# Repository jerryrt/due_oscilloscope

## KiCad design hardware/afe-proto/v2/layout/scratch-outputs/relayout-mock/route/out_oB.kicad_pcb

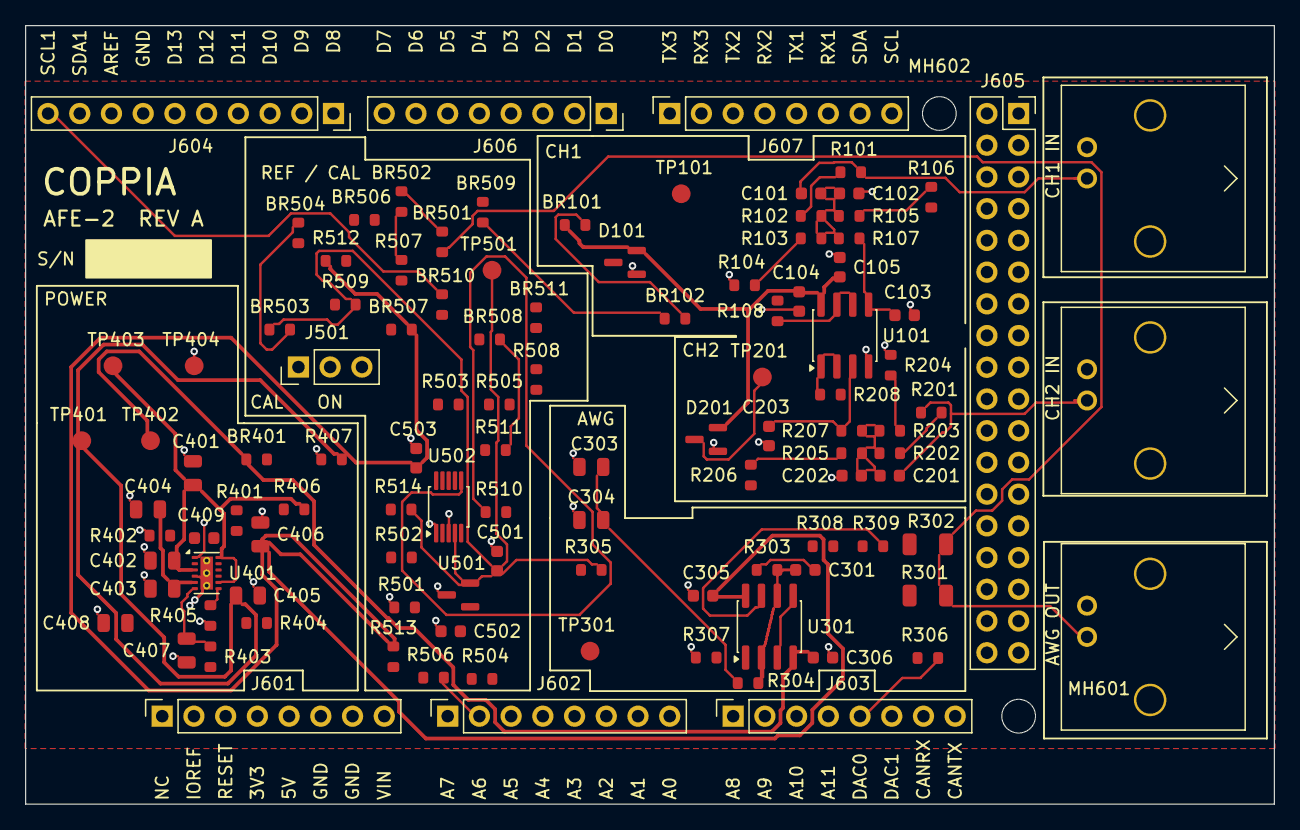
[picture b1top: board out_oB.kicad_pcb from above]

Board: 2 copper layers, 100.0 x 62.3 mm, 112 parts (0 on the bottom side), 61 nets.

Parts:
BR101, BR102, BR401, BR501, BR502, BR503, BR504, BR506, BR507, BR508, BR509, BR510, BR511: 0R; R_0603_1608Metric
C101, C201: 18p C0G; C_0603_1608Metric
C102, C202: 47p C0G; C_0603_1608Metric
C103, C203, C301: 10p C0G; C_0603_1608Metric
C104, C305, C306, C502, C503: 100n X7R; C_0603_1608Metric
C105, C409, C501: 1u X5R; C_0603_1608Metric
C303, C304, C401, C402, C403, C404, C405, C406, C407, C408: 10u X5R 25V; C_0805_2012Metric
D101, D201: BAV99; SOT-23
J101, J201, J301: KH-BNC50-3511; BNC_Kinghelm_KH-BNC50-3511_Horizontal
J501: CAL; PinHeader_1x03_P2.54mm_Vertical
J601: POWER0; PinSocket_1x08_P2.54mm_Vertical
J602: ADCL0; PinSocket_1x08_P2.54mm_Vertical
J603: ADCH0; PinSocket_1x08_P2.54mm_Vertical
J604: PWMH0; PinSocket_1x10_P2.54mm_Vertical
J605: XIO0; PinSocket_2x18_P2.54mm_Vertical_DueXIO
J606: PWML0; PinSocket_1x08_P2.54mm_Vertical
J607: COMMUNICATION0; PinSocket_1x08_P2.54mm_Vertical
MH601, MH602: M2.5 standoff; MountingHole_2.7mm_M2.5
R101, R103, R201, R203: 470k 1%; R_0603_1608Metric
R102, R202: 300k 1%; R_0603_1608Metric
R104, R105, R204, R205: 330k 1%; R_0603_1608Metric
R106, R206, R514: 0R; R_0603_1608Metric
R107, R207: 470R 1%; R_0603_1608Metric
R108, R208: 22R 1%; R_0603_1608Metric
R301, R302: 100R 1%; R_1206_3216Metric
R303, R304, R306: 3k 1%; R_0603_1608Metric
R305: 150R 1%; R_0603_1608Metric
R307: 27k 1%; R_0603_1608Metric
R308, R309, R406: 1R 1%; R_0603_1608Metric
R401: 120k 1%; R_0603_1608Metric
R402: 68k 1%; R_0603_1608Metric
R403: 56k 1%; R_0603_1608Metric
R404: 8.2k 1%; R_0603_1608Metric
R405: 100k 1%; R_0603_1608Metric
R407: 1.8k 1%; R_0603_1608Metric
R501, R502, R503, R504, R505, R506: 330R 1%; R_0603_1608Metric
R507: 15k 1%; R_0603_1608Metric
R508, R511: 10k 1%; R_0603_1608Metric
R509: 1k 1%; R_0603_1608Metric
R510: 3.9k 1%; R_0603_1608Metric
R512, R513: 4.7k 1%; R_0603_1608Metric
TP101: A1; TestPoint_Pad_D1.5mm
TP201: A0; TestPoint_Pad_D1.5mm
TP301: AWG_OUT; TestPoint_Pad_D1.5mm
TP401: +3V3A; TestPoint_Pad_D1.5mm
TP402: VNEG; TestPoint_Pad_D1.5mm
TP403: +5V_F; TestPoint_Pad_D1.5mm
TP404: GND; TestPoint_Pad_D1.5mm
TP501: VREF; TestPoint_Pad_D1.5mm
U101, U301: TPH2502-SR; SOIC-8_3.9x4.9mm_P1.27mm
U401: LM27762DSSR; WSON-12-1EP_3x2mm_P0.5mm_EP1x2.65_ThermalVias
U501: REF3030EAIDBZR; SOT-23
U502: ADS1115IDGSR; MSOP-10_3x3mm_P0.5mm

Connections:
/+3V3A: BR507.2, BR509.1, C305.1, C405.1, C406.1, C503.1, R401.1, R407.1, R512.1, R513.1, TP401.1, U301.8, U401.11, U502.8
/+3V3A_K: BR102.1, BR509.2
/+3V3A_R: BR507.1, C502.1, U501.1
/+3V3A_S: BR101.1, BR102.2
/+3V3A_U: BR101.2, C104.1, C105.1, D101.2, D201.2, U101.8
/+5V_DUE: J601.5, R406.1
/+5V_F: C401.1, C402.1, R406.2, TP403.1, U401.3, U401.8, U401.12
/A0: D201.3, J602.8, R208.2, TP201.1
/A1: D101.3, J602.7, R108.2, TP101.1
/ADS_B: R511.2, U502.7
/ADS_TAP: R510.2, U502.6
/AREF: J604.8, R514.2
/AWG_BIN: R306.2, R307.1, U301.3, U301.5
/AWG_BNC: BR501.2, J301.1, R301.2, R302.2
/AWG_BNC_L: BR502.1, R507.1
/AWG_BNC_M: BR501.1, BR502.2
/AWG_FB: C301.2, R303.2, R304.1, U301.2, U301.6
/AWG_OA: R308.1, U301.1
/AWG_OB: R309.1, U301.7
/AWG_VO: C301.1, R301.1, R302.1, R303.1, R308.2, R309.2, TP301.1
/AWG_VREF: C303.1, C304.1, R304.2, R305.2
/CH1_IN: C101.1, J101.1, R101.1
/CH1_M1: R101.2, R102.1
/CH1_M2: R103.2, R104.1
/CH1_M3: R105.2, R106.1
/CH1_N: C101.2, C102.1, R102.2, R103.1, R105.1, R107.1
/CH1_NP: C103.1, R107.2, U101.5
/CH1_OUT: R108.1, U101.6, U101.7
/CH2_IN: C201.1, J201.1, R201.1
/CH2_M1: R201.2, R202.1
/CH2_M2: R203.2, R204.1
/CH2_M3: R205.2, R206.1
/CH2_N: C201.2, C202.1, R202.2, R203.1, R205.1, R207.1
/CH2_NP: C203.1, R207.2, U101.3
/CH2_OUT: R208.1, U101.1, U101.2
/DAC0: J603.5, R306.1
/GND: C102.2, C103.2, C104.2, C105.2, C202.2, C203.2, C303.2, C304.2, C305.2, C306.2, C401.2, C402.2, C403.2, C404.2, C405.2, C406.2, C407.2, C408.2, C501.2, C502.2, C503.2, D101.1, D201.1, J101.2, J201.2, J301.2, J601.6, J601.7, J604.7, J605.35, J605.36, R104.2, R204.2, R307.2, R402.2, R405.2, R407.2, R501.1, TP404.1, U101.4, U401.1, U401.4, U401.13, U501.3, U502.1, U502.3
/LM_C1N: C409.2, U401.9
/LM_C1P: C409.1, U401.10
/LM_CP: C403.1, C404.1, U401.5
/LM_FB3M: R403.2, R404.1
/LM_FBN: R404.2, R405.1, U401.7
/LM_FBP: R401.2, R402.1, U401.2
/SCL: BR510.1, J604.10, R513.2
/SCL_A: BR510.2, U502.10
/SDA: BR511.1, J604.9
/SDA_A: BR511.2, R512.2, U502.9
/SNS_B: BR508.1, J501.2
/SNS_B_N: BR508.2, R508.2, R509.1, R511.1
/SNS_T0: R507.2, R508.1, R510.1
/TAP1: J602.6, R501.2, R502.1
/TAP2: J602.5, R502.2, R503.1
/TAP3: J501.3, J602.4, R503.2, R504.1
/TAP4: BR506.1, J501.1, J602.3, R504.2, R505.1
/TAP4_A: BR506.2, U502.5
/TAP5: J602.2, R505.2, R506.1
/VNEG: BR401.2, C306.1, TP402.1, U301.4
/VNEG_G: BR401.1, C407.1, C408.1, R403.1, U401.6
/VREF: BR503.1, C501.1, J602.1, R106.2, R305.1, R506.2, R509.2, R514.1, TP501.1, U501.2, U502.4
/VREF_M: BR503.2, BR504.1
/VREF_P: BR504.2, R206.2

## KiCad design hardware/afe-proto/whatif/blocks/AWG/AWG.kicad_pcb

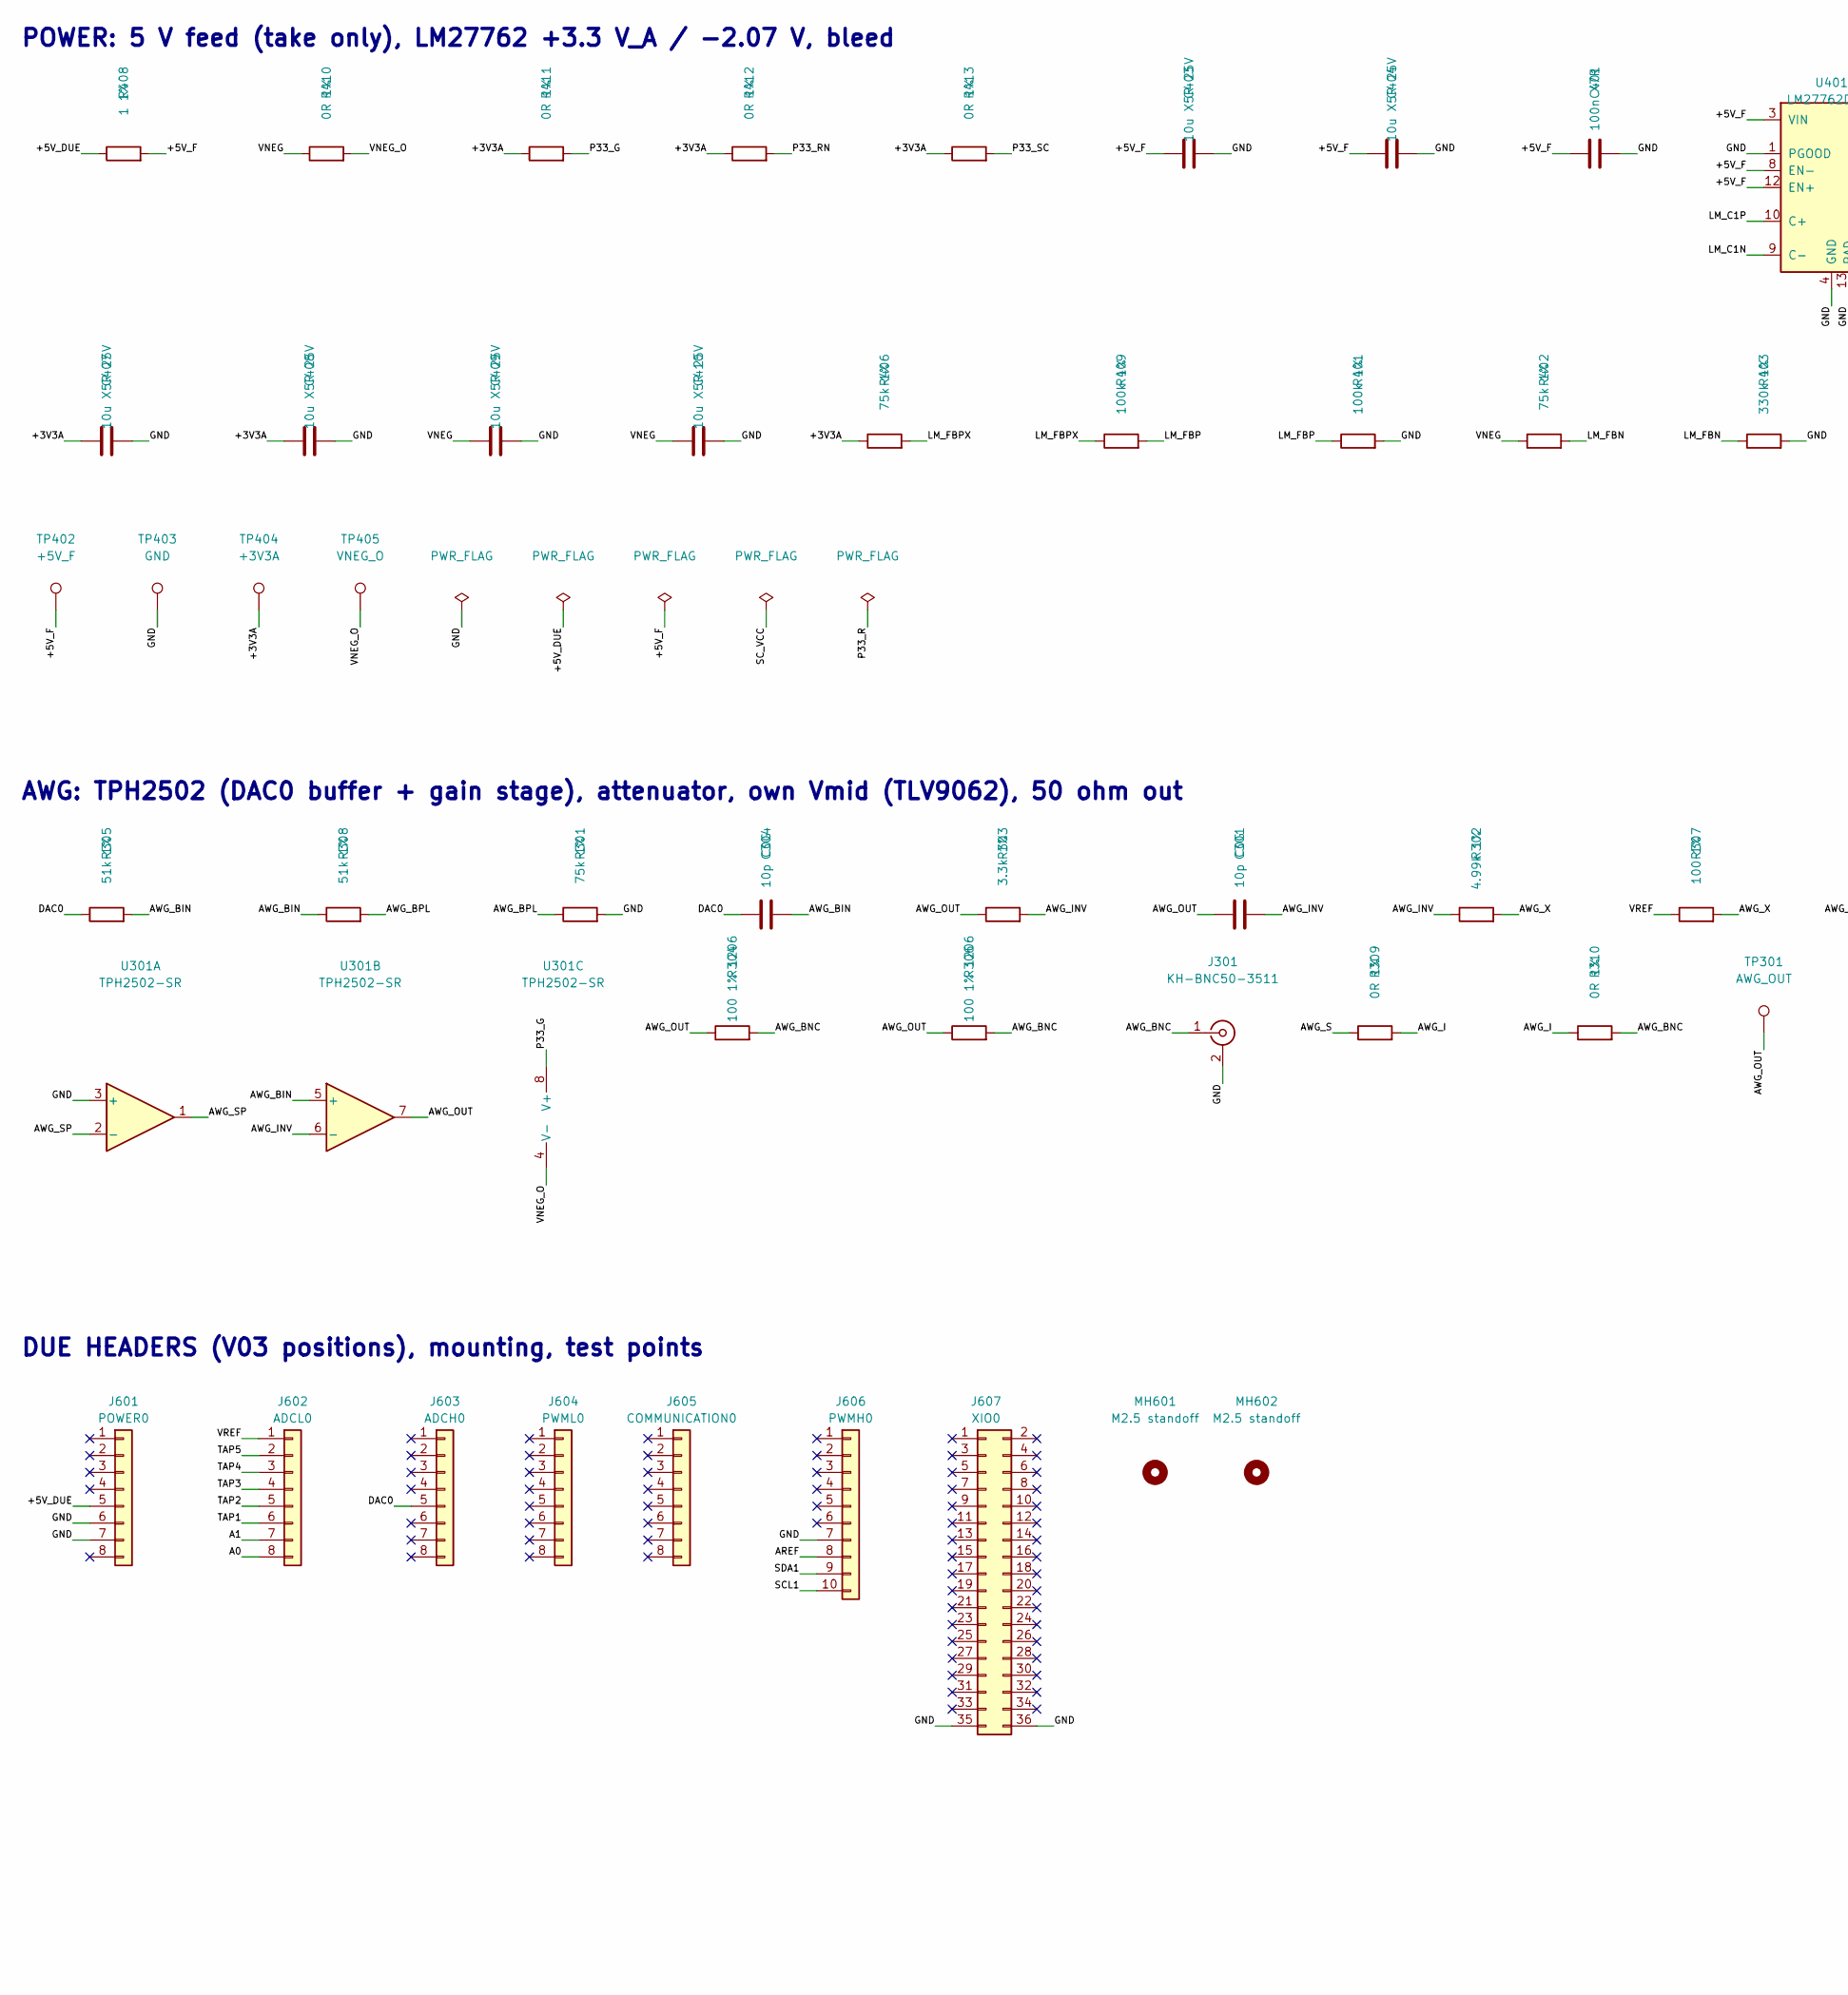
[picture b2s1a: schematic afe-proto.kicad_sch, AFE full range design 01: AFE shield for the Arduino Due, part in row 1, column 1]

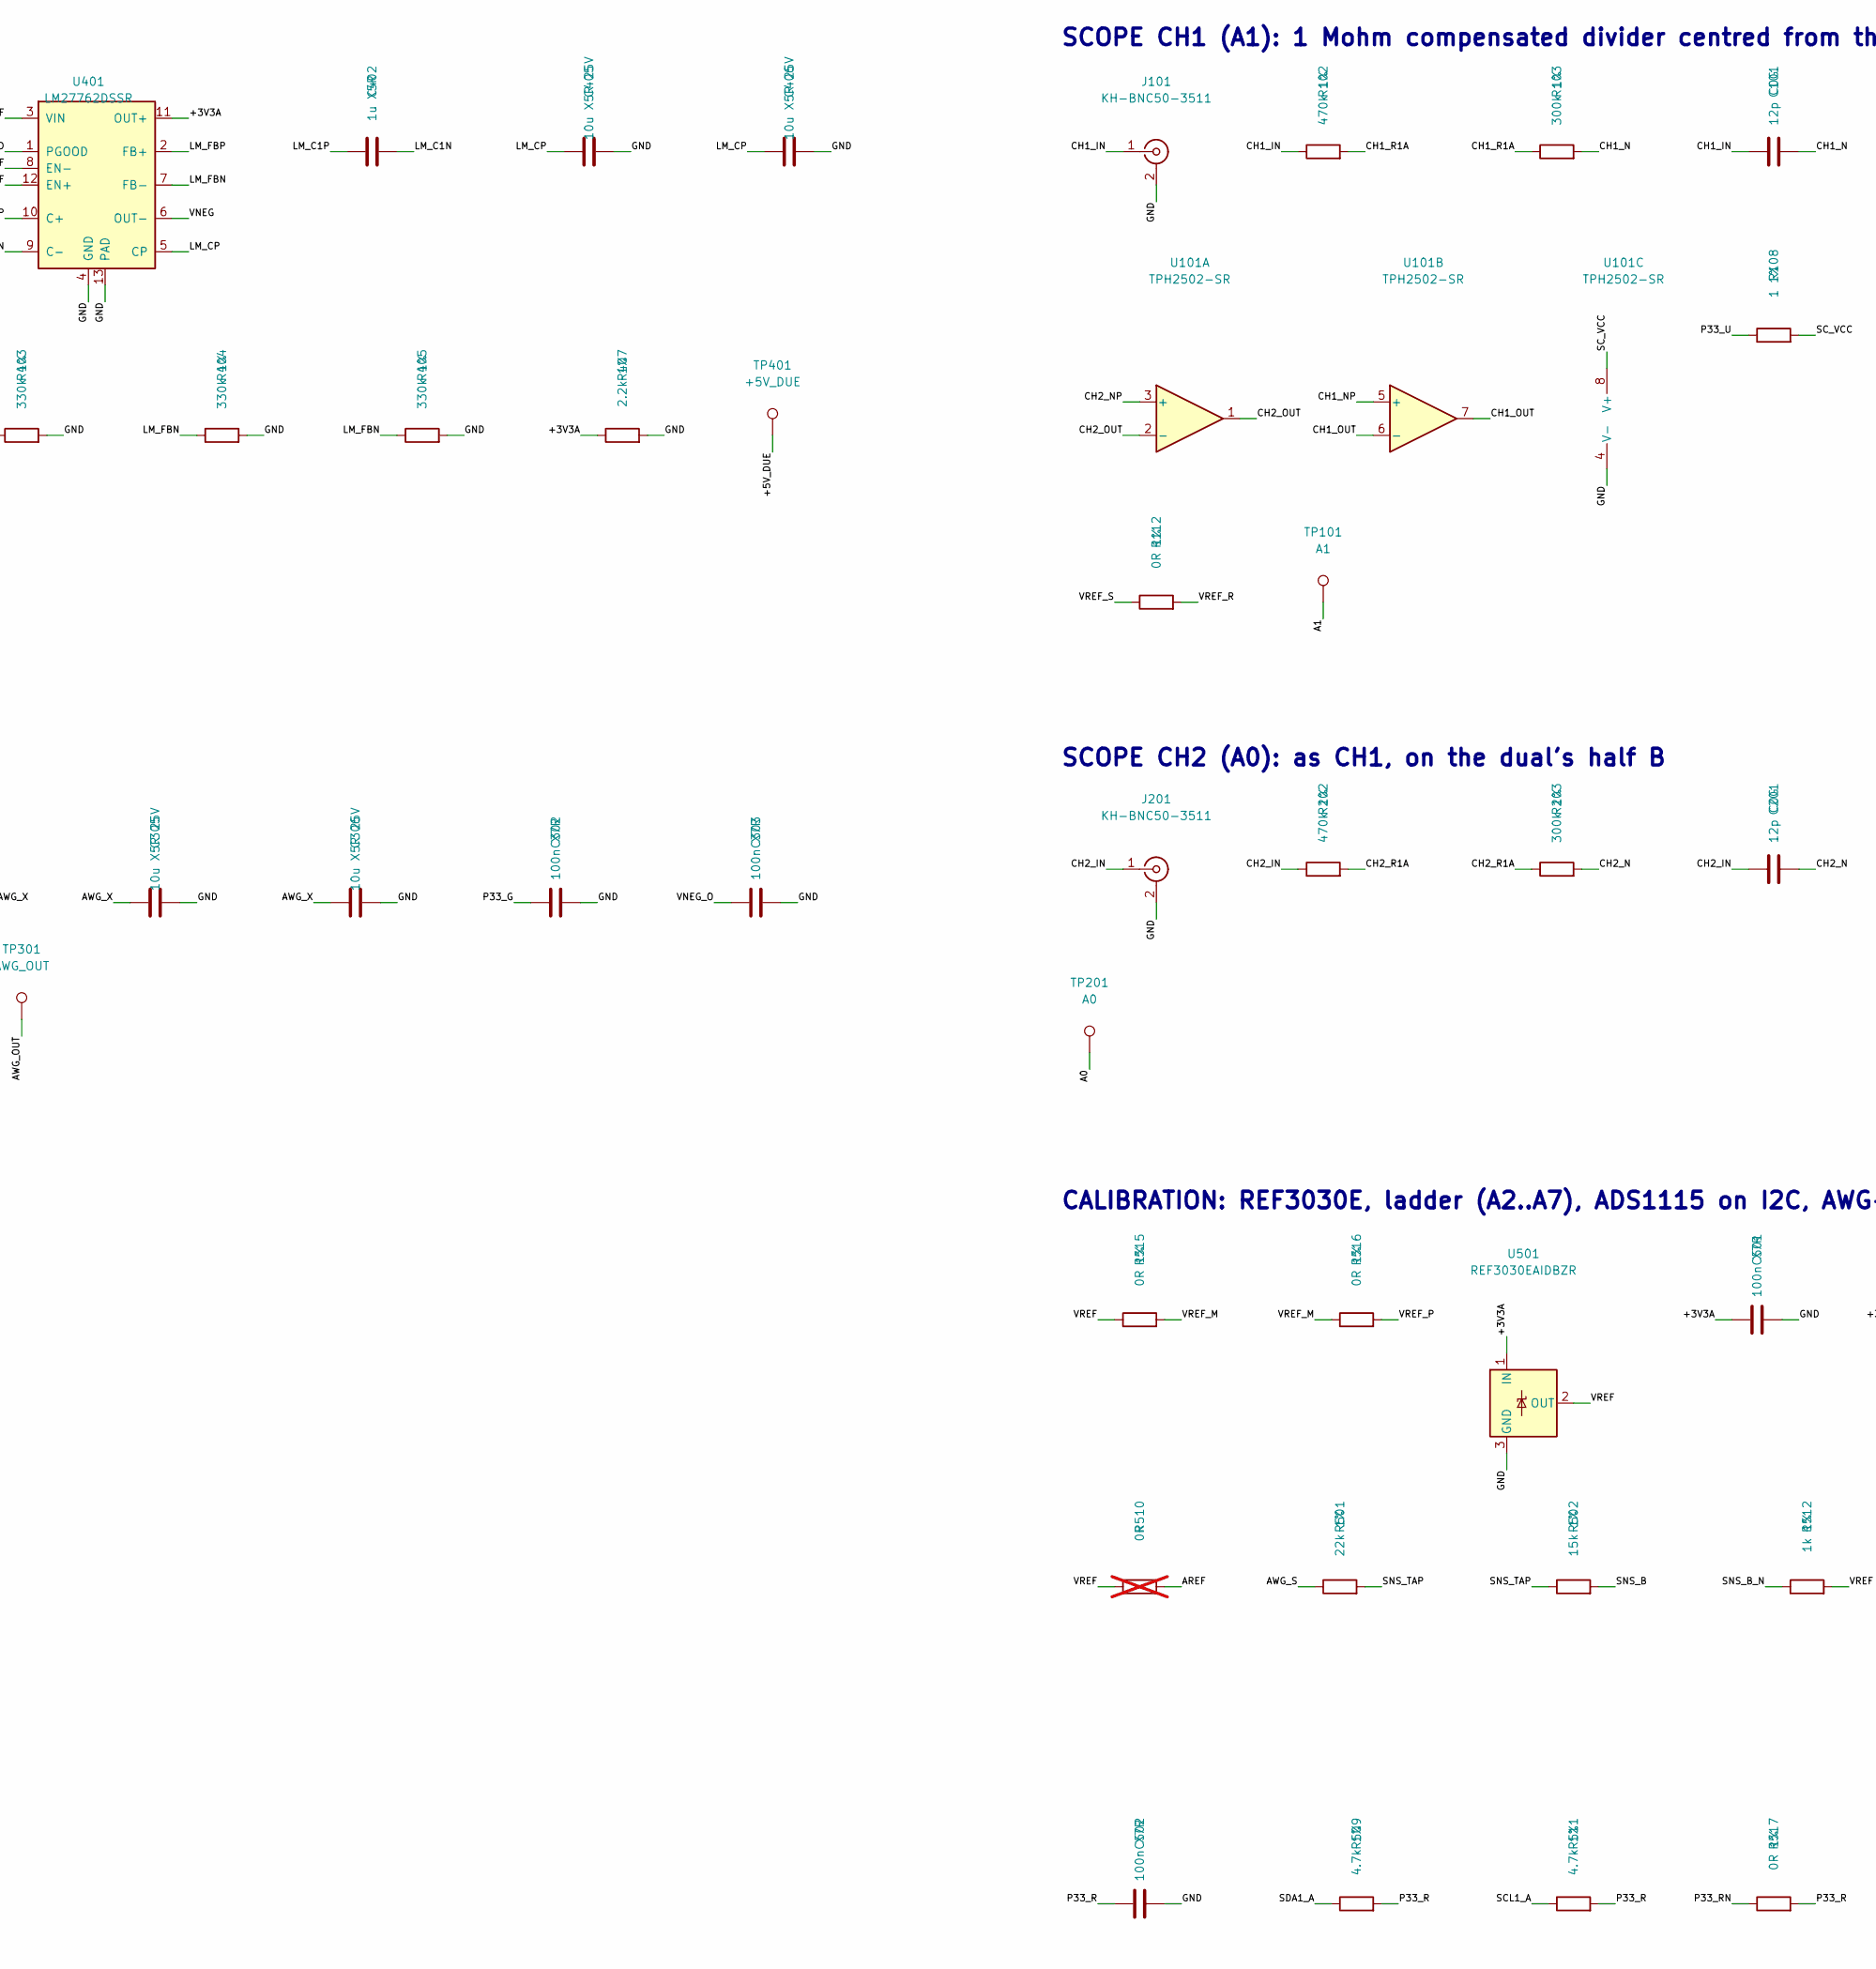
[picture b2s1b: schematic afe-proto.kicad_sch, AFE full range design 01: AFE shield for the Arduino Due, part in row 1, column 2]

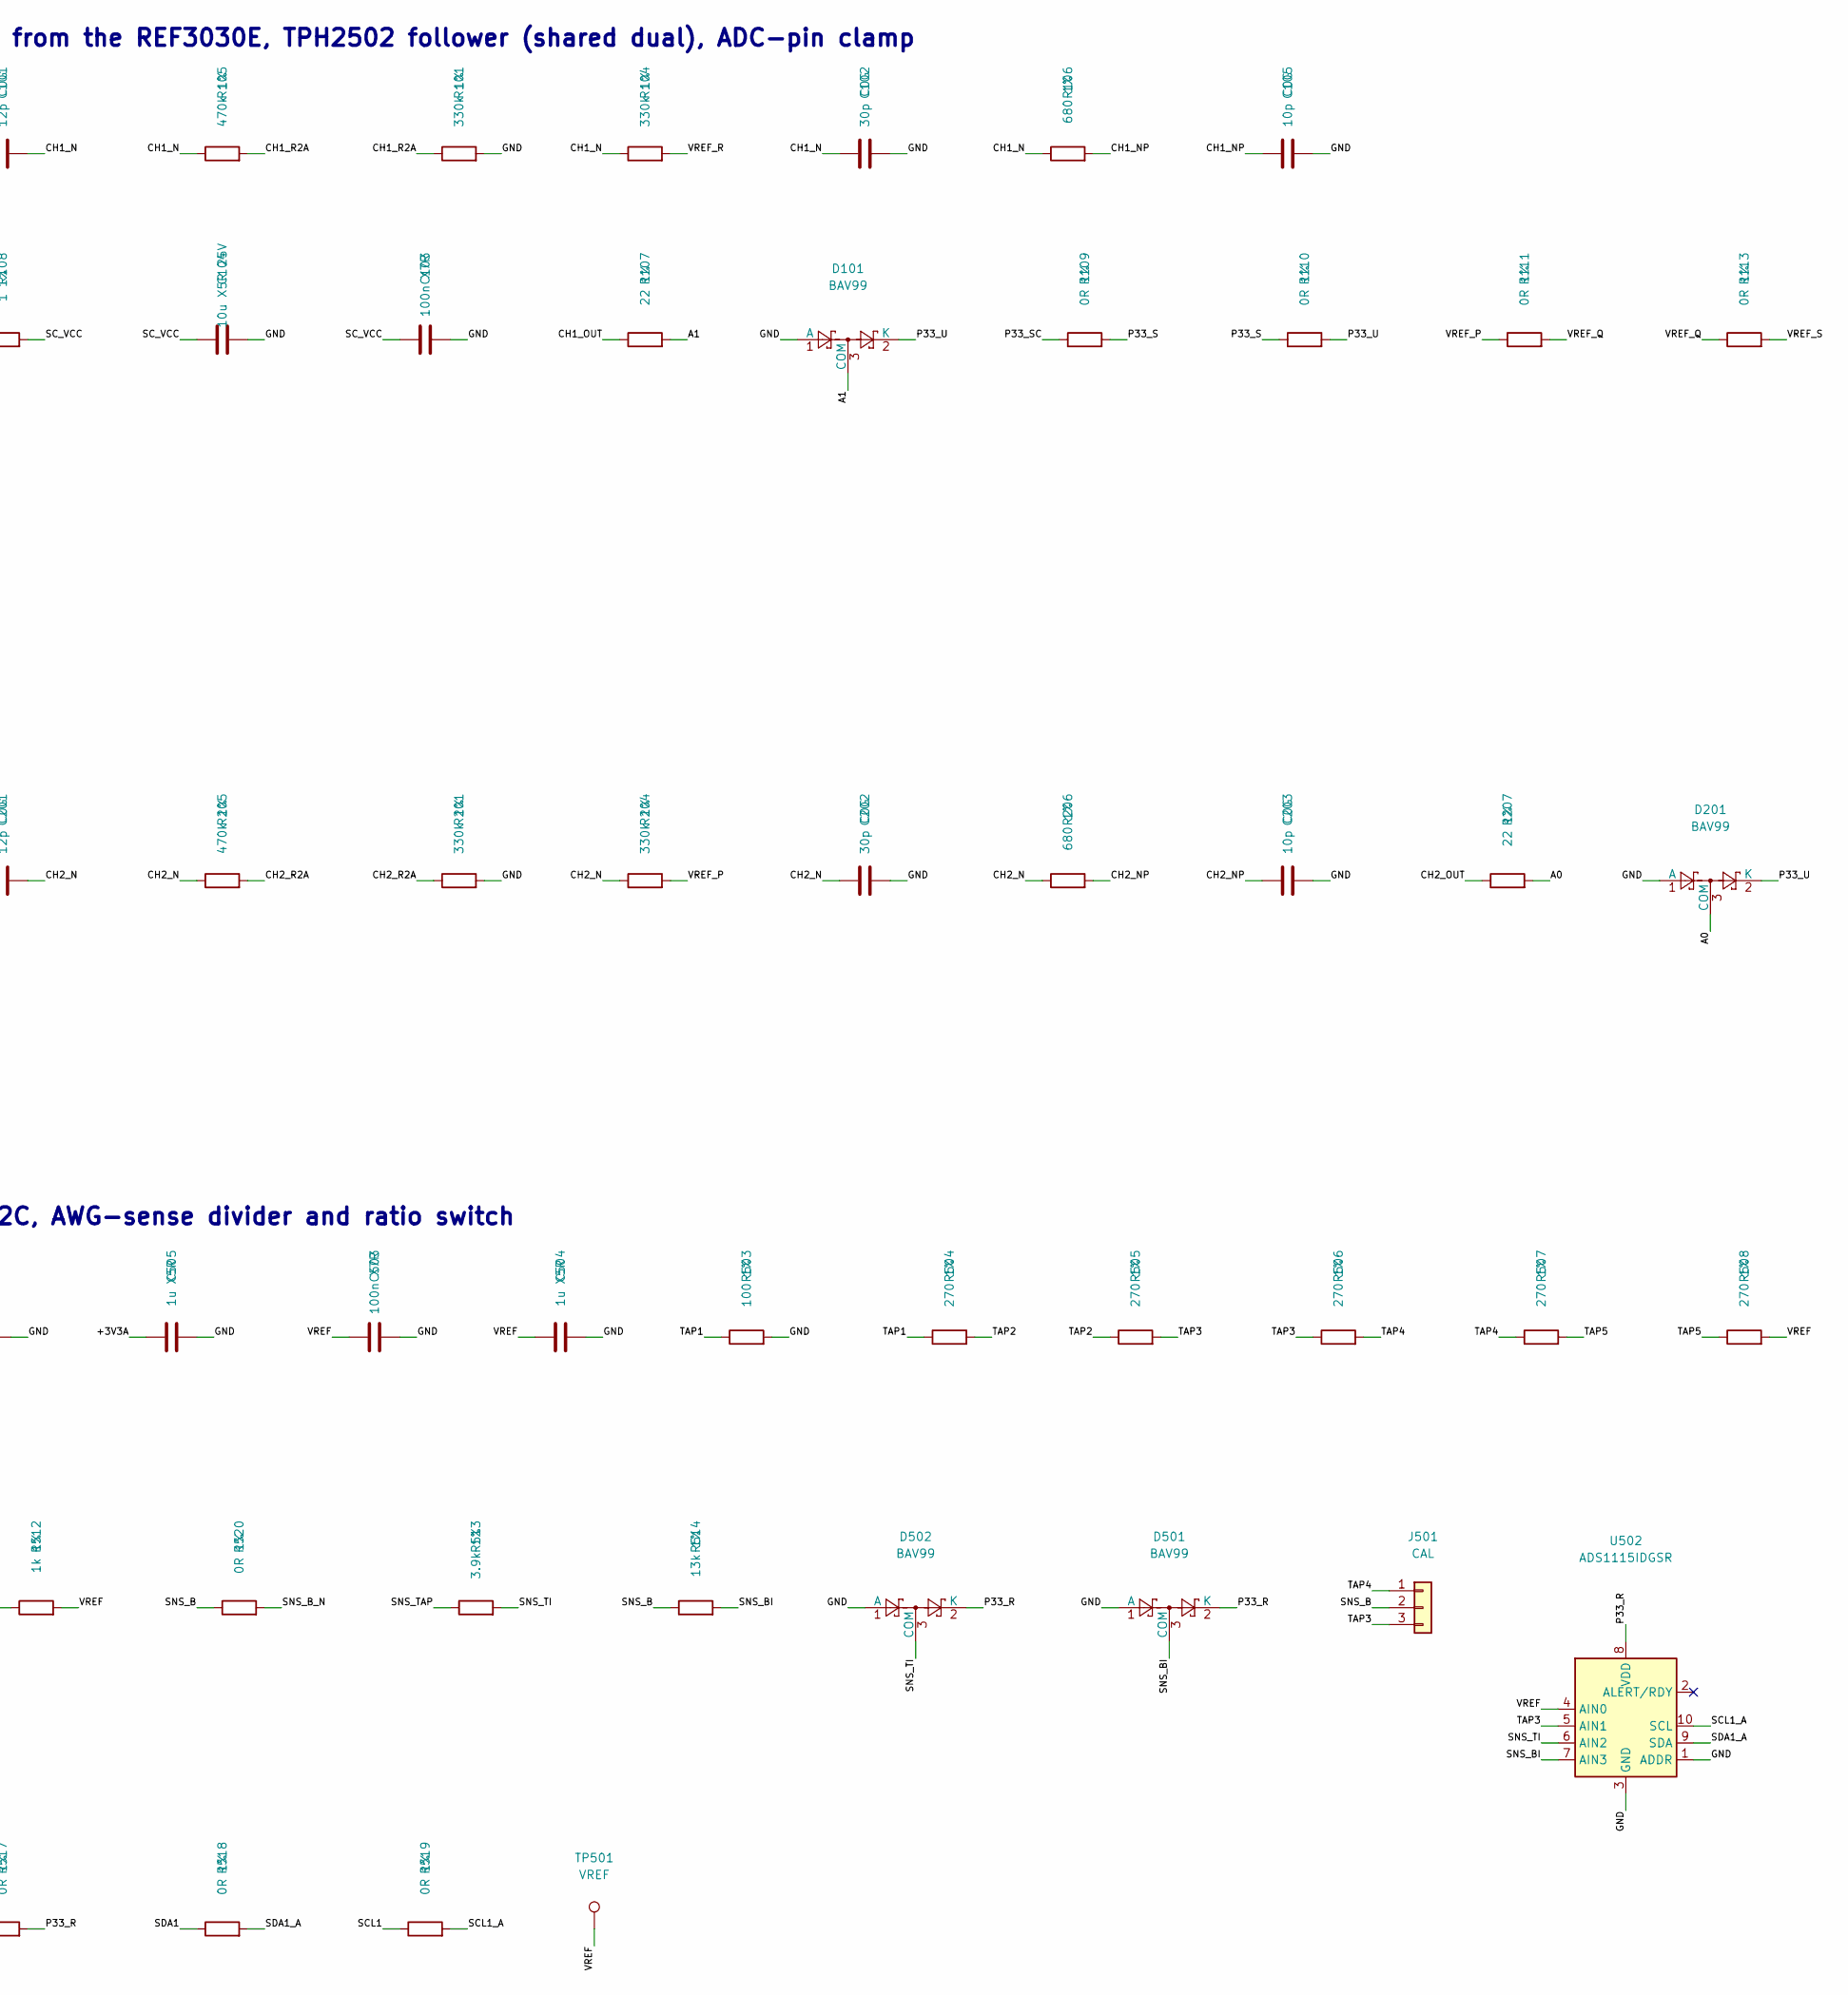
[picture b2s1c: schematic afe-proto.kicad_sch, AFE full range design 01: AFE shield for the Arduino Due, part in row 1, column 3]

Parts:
C101, C201: 12p C0G; C_0603_1608Metric; MPN Samsung CL10C120JB8NNNC; LCSC C38523
C102, C202: 30p C0G; C_0603_1608Metric; MPN FH 0603CG300J500NT; LCSC C1658
C103, C302, C303, C401, C501, C502, C503: 100n X7R; C_0603_1608Metric; MPN Yageo CC0603KRX7R9BB104; LCSC C14663
C104, C305, C306, C403, C404, C405, C406, C407, C408, C409, C410: 10u X5R 25V; C_0805_2012Metric; MPN Samsung CL21A106KAYNNNE; LCSC C15850
C105, C203, C301, C304: 10p C0G; C_0603_1608Metric; MPN Samsung CL10C100JB8NNNC; LCSC C1634
C402, C504, C505: 1u X5R; C_0603_1608Metric; MPN Samsung CL10A105KB8NNNC; LCSC C15849
D101, D201, D501, D502: BAV99; SOT-23; MPN Nexperia BAV99,215; LCSC C2500
J101, J201, J301: KH-BNC50-3511; BNC_Kinghelm_KH-BNC50-3511_Horizontal; MPN Kinghelm KH-BNC50-3511; LCSC C2837587
J501: CAL; PinHeader_1x03_P2.54mm_Vertical
J601: POWER0; PinSocket_1x08_P2.54mm_Vertical
J602: ADCL0; PinSocket_1x08_P2.54mm_Vertical
J603: ADCH0; PinSocket_1x08_P2.54mm_Vertical
J604: PWML0; PinSocket_1x08_P2.54mm_Vertical
J605: COMMUNICATION0; PinSocket_1x08_P2.54mm_Vertical
J606: PWMH0; PinSocket_1x10_P2.54mm_Vertical
J607: XIO0; PinSocket_2x18_P2.54mm_Vertical_DueXIO
MH601, MH602: M2.5 standoff; MountingHole_2.7mm_M2.5
R101, R104, R201, R204, R403, R404, R405: 330k 1%; R_0603_1608Metric; MPN UNI-ROYAL 0603WAF3303T5E; LCSC C23137
R102, R105, R202, R205: 470k 1%; R_0603_1608Metric; MPN UNI-ROYAL 0603WAF4703T5E; LCSC C23178
R103, R203: 300k 1%; R_0603_1608Metric; MPN UNI-ROYAL 0603WAF3003T5E; LCSC C23024
R106, R206: 680 1%; R_0603_1608Metric; MPN UNI-ROYAL 0603WAF6800T5E; LCSC C23228
R107, R207: 22 1%; R_0603_1608Metric; MPN UNI-ROYAL 0603WAF220JT5E; LCSC C23345
R108, R408: 1 1%; R_0603_1608Metric; MPN UNI-ROYAL 0603WAF100KT5E; LCSC C22936
R109, R110, R111, R112, R113, R309, R310, R410, R411, R412, R413, R515, R516, R517, R518, R519, R520: 0R 1%; R_0603_1608Metric; MPN UNI-ROYAL 0603WAF0000T5E; LCSC C21189
R301, R402, R406: 75k 1%; R_0603_1608Metric; MPN UNI-ROYAL 0603WAF7502T5E; LCSC C23242
R302: 4.99k 1%; R_0603_1608Metric; MPN UNI-ROYAL 0603WAF4991T5E; LCSC C23046
R303: 3.3k 1%; R_0603_1608Metric; MPN UNI-ROYAL 0603WAF3301T5E; LCSC C22978
R304, R306: 100 1% 1206; R_1206_3216Metric; MPN UNI-ROYAL 1206W4F1000T5E; LCSC C17901
R305, R308: 51k 1%; R_0603_1608Metric; MPN UNI-ROYAL 0603WAF5102T5E; LCSC C23196
R307, R503: 100 1%; R_0603_1608Metric; MPN UNI-ROYAL 0603WAF1000T5E; LCSC C22775
R401, R409: 100k 1%; R_0603_1608Metric; MPN UNI-ROYAL 0603WAF1003T5E; LCSC C25803
R407: 2.2k 1%; R_0603_1608Metric; MPN UNI-ROYAL 0603WAF2201T5E; LCSC C4190
R501: 22k 1%; R_0603_1608Metric; MPN UNI-ROYAL 0603WAF2202T5E; LCSC C31850
R502: 15k 1%; R_0603_1608Metric; MPN UNI-ROYAL 0603WAF1502T5E; LCSC C22809
R504, R505, R506, R507, R508: 270 1%; R_0603_1608Metric; MPN UNI-ROYAL 0603WAF2700T5E; LCSC C22966
R509, R511: 4.7k 1%; R_0603_1608Metric; MPN UNI-ROYAL 0603WAF4701T5E; LCSC C23162
R510: 0R; R_0603_1608Metric; not fitted
R512: 1k 1%; R_0603_1608Metric; MPN UNI-ROYAL 0603WAF1001T5E; LCSC C21190
R513: 3.9k 1%; R_0603_1608Metric; MPN UNI-ROYAL 0603WAF3901T5E; LCSC C23018
R514: 13k 1%; R_0603_1608Metric; MPN UNI-ROYAL 0603WAF1302T5E; LCSC C22797
TP101: A1; TestPoint_Pad_D1.0mm
TP201: A0; TestPoint_Pad_D1.0mm
TP301: AWG_OUT; TestPoint_Pad_D1.0mm
TP401: +5V_DUE; TestPoint_Pad_D1.0mm
TP402: +5V_F; TestPoint_Pad_D1.0mm
TP403: GND; TestPoint_Pad_D1.0mm
TP404: +3V3A; TestPoint_Pad_D1.0mm
TP405: VNEG_O; TestPoint_Pad_D1.0mm
TP501: VREF; TestPoint_Pad_D1.0mm
U101, U301: TPH2502-SR; SOIC-8_3.9x4.9mm_P1.27mm; MPN 3PEAK TPH2502-SR; LCSC C118223
U401: LM27762DSSR; WSON-12-1EP_3x2mm_P0.5mm_EP1x2.65_ThermalVias; MPN TI LM27762DSSR; LCSC C473398
U501: REF3030EAIDBZR; SOT-23; MPN TI REF3030EAIDBZR; LCSC C54120492
U502: ADS1115IDGSR; TSSOP-10_3x3mm_P0.5mm; MPN TI ADS1115IDGSR; LCSC C37593

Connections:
/+5V_DUE: J601.5, R408.1, TP401.1
/+5V_F: C401.1, C403.1, C404.1, R408.2, TP402.1, U401.3 (VIN), U401.8 (EN-), U401.12 (EN+)
/A0: D201.3 (COM), J602.8, R207.2, TP201.1
/A1: D101.3 (COM), J602.7, R107.2, TP101.1
/AREF: J606.8, R510.2
/AWG_BIN: C304.2, R305.2, R308.1, U301.5 (+)
/AWG_BNC: J301.1 (In), R304.2, R306.2, R310.2
/AWG_BPL: R301.1, R308.2
/AWG_I: R309.2, R310.1
/AWG_INV: C301.2, R302.1, R303.2, U301.6 (-)
/AWG_OUT: C301.1, R303.1, R304.1, R306.1, TP301.1, U301.7
/AWG_S: R309.1, R501.1
/AWG_SP: U301.1, U301.2 (-)
/AWG_X: C305.1, C306.1, R302.2, R307.2
/CH1_IN: C101.1, J101.1 (In), R102.1
/CH1_N: C101.2, C102.1, R103.2, R104.1, R105.1, R106.1
/CH1_NP: C105.1, R106.2, U101.5 (+)
/CH1_OUT: R107.1, U101.6 (-), U101.7
/CH1_R1A: R102.2, R103.1
/CH1_R2A: R101.1, R105.2
/CH2_IN: C201.1, J201.1 (In), R202.1
/CH2_N: C201.2, C202.1, R203.2, R204.1, R205.1, R206.1
/CH2_NP: C203.1, R206.2, U101.3 (+)
/CH2_OUT: R207.1, U101.1, U101.2 (-)
/CH2_R1A: R202.2, R203.1
/CH2_R2A: R201.1, R205.2
/DAC0: C304.1, J603.5, R305.1
/GND: C102.2, C103.2, C104.2, C105.2, C202.2, C203.2, C302.2, C303.2, C305.2, C306.2, C401.2, C403.2, C404.2, C405.2, C406.2, C407.2, C408.2, C409.2, C410.2, C501.2, C502.2, C503.2, C504.2, C505.2, D101.1 (A), D201.1 (A), D501.1 (A), D502.1 (A), J101.2 (Ext), J201.2 (Ext), J301.2 (Ext), J601.6, J601.7, J606.7, J607.35, J607.36, R101.2, R201.2, R301.2, R401.2, R403.2, R404.2, R405.2, R407.2, R503.2, TP403.1, U101.4 (V-), U301.3 (+), U401.1 (PGOOD), U401.4 (GND), U401.13 (PAD), U501.3 (GND), U502.1 (ADDR), U502.3 (GND)
/LM_C1N: C402.2, U401.9 (C-)
/LM_C1P: C402.1, U401.10 (C+)
/LM_CP: C405.1, C406.1, U401.5 (CP)
/LM_FBN: R402.2, R403.1, R404.1, R405.1, U401.7 (FB-)
/LM_FBP: R401.1, R409.2, U401.2 (FB+)
/LM_FBPX: R406.2, R409.1
/P33_R: C502.1, D501.2 (K), D502.2 (K), R509.2, R511.2, R517.2, U502.8 (VDD)
/P33_S: R109.2, R110.1
/P33_U: D101.2 (K), D201.2 (K), R108.1, R110.2
/SCL1: J606.10, R519.1
/SCL1_A: R511.1, R519.2, U502.10 (SCL)
/SC_VCC: C103.1, C104.1, R108.2, U101.8 (V+)
/SDA1: J606.9, R518.1
/SDA1_A: R509.1, R518.2, U502.9 (SDA)
/SNS_B: J501.2, R502.2, R514.1, R520.1
/SNS_BI: D501.3 (COM), R514.2, U502.7 (AIN3)
/SNS_B_N: R512.1, R520.2
/SNS_TAP: R501.2, R502.1, R513.1
/SNS_TI: D502.3 (COM), R513.2, U502.6 (AIN2)
/TAP1: J602.6, R503.1, R504.1
/TAP2: J602.5, R504.2, R505.1
/TAP3: J501.3, J602.4, R505.2, R506.1, U502.5 (AIN1)
/TAP4: J501.1, J602.3, R506.2, R507.1
/TAP5: J602.2, R507.2, R508.1
/VNEG: C409.1, C410.1, R402.1, R410.1, U401.6 (OUT-)
/VNEG_O: C303.1, R410.2, TP405.1, U301.4 (V-)
/VREF: C503.1, C504.1, J602.1, R307.1, R508.2, R510.1, R512.2, R515.1, TP501.1, U501.2 (OUT), U502.4 (AIN0)
/VREF_M: R515.2, R516.1
/VREF_P: R111.1, R204.2, R516.2
/VREF_Q: R111.2, R113.1
/VREF_R: R104.2, R112.2
/VREF_S: R112.1, R113.2

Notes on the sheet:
POWER: 5 V feed (take only), LM27762 +3.3 V_A / -2.07 V, bleed
SCOPE CH1 (A1): 1 Mohm compensated divider centred from the REF3030E, TPH2502 follower (shared dual), ADC-pin clamp
SCOPE CH2 (A0): as CH1, on the dual's half B
AWG: TPH2502 (DAC0 buffer + gain stage), attenuator, own Vmid (TLV9062), 50 ohm out
CALIBRATION: REF3030E, ladder (A2..A7), ADS1115 on I2C, AWG-sense divider and ratio switch
DUE HEADERS (V03 positions), mounting, test points

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
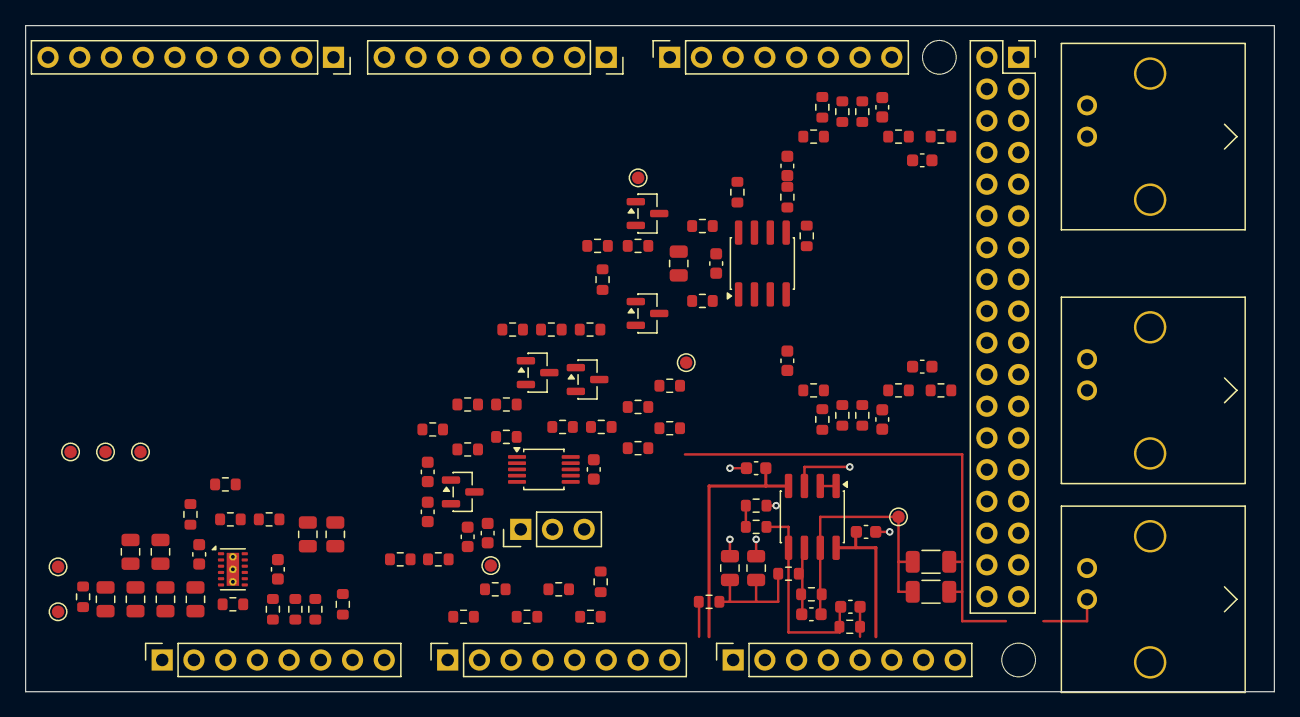
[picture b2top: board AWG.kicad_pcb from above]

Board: 2 copper layers, 100.0 x 53.3 mm, 120 parts (0 on the bottom side), 61 nets.

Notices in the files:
hardware/afe-proto/v2/layout/scratch-outputs/relayout-mock/route/out_oB.kicad_pcb:
Own work, CC BY-SA 4.0
